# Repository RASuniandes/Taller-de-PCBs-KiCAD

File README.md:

# Taller de PCBs KiCAD — RAS x CERES
**Proyecto de taller (Carrito con ESP32-S3)** · 
23-09-2024: **RAS Day** 🎉

Este repo contiene el material del taller colaborativo **RAS x CERES** de diseño de PCBs en KiCAD:
- Proyecto KiCad listo para abrir (v8+).
- Librerías de símbolos y huellas *incluidas* (rutas relativas).
- Reglas de diseño (DRC) configurables para JLCPCB.
- Gerbers de ejemplo y BOM.

## 🧩 Hardware del proyecto
- **MCU:** ESP32-S3 DevKit C1 (módulo, footprint incluido).
- **IMU:** MPU6050 (módulo).
- **Motores:** Módulo **DRV8833** (Driver de Motores).
- **Expansión I²C:** 3 conectores **JST-XH 4 pines** (VCC, GND, SDA, SCL).
- **Power & Actuadores:**
  - Bornera de tornillo para **batería** (2 + 2 pines).
  - Borneras de tornillo para **motores** (2×2 pines o 2× de 2 pines).

> **Tip de ruta**: el ESP32-S3 DevKit C1 aquí se usa como *módulo* (no el chip suelto), para acelerar footprinting y montaje.

## ⚙️ Requisitos
- **KiCad 8.x** (recomendado).
- Sin dependencias externas: librerías incluidas y referenciadas de forma **relativa**.

## 🚀 Uso rápido
```bash
# 1) Clona
git clone https://github.com/<tu-org-o-user>/Taller-PCBs-KiCAD-RASxCERES.git
cd Taller-PCBs-KiCAD-RASxCERES
```
🧭 Flujo de trabajo en el taller

  1) Esquemático (.kicad_sch):
      Bloques: ESP32S3, DRV8833, I2C_Expanders (3× JST-XH 4p), Power, MPU6050, (opcional) Color.
  
  2) Net labels claras: I2C_SDA, I2C_SCL, M1_A, M1_B, M2_A, M2_B, VBAT, 5V, 3V3, GND.
  3) Asignación de huellas (ya pre-asignadas; revisar conflictos si cambias referencias).
  4) Reglas/DRC: cargar kicad/rules/jlcpcb.kicad_dru.
  5) Ruteo: intenta mantener I²C corto y motores con pistas anchas.
  6) Fabricación: exporta Gerbers a kicad/fabrication/ o usa los de ejemplo

🤝 Créditos

Taller colaborativo [(RAS)](https://www.instagram.com/ras_uniandes/?hl=en) x CERES [(@ceres.robotics)](https://www.instagram.com/ceres.robotics/?hl=en)

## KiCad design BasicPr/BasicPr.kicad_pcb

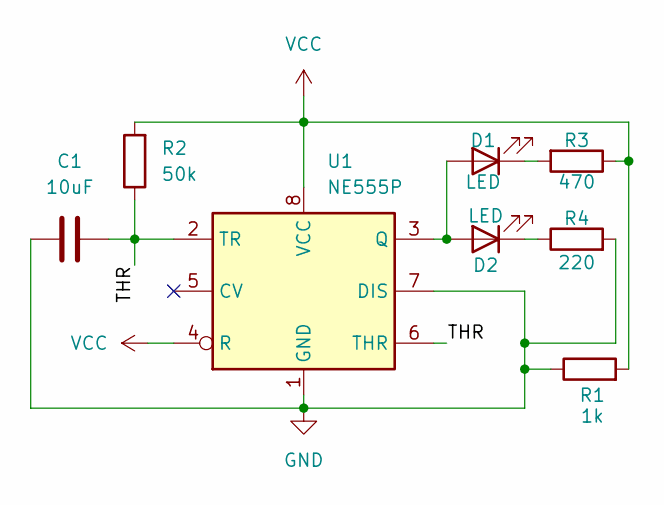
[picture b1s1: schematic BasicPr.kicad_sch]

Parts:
C1: 10uF; CP_Radial_D5.0mm_P2.50mm
D1, D2: LED; LED_D3.0mm_Horizontal_O1.27mm_Z10.0mm
R1: 1k; R_Axial_DIN0204_L3.6mm_D1.6mm_P7.62mm_Horizontal
R2: 50k; R_Axial_DIN0204_L3.6mm_D1.6mm_P7.62mm_Horizontal
R3: 470; R_Axial_DIN0204_L3.6mm_D1.6mm_P7.62mm_Horizontal
R4: 220; R_Axial_DIN0204_L3.6mm_D1.6mm_P7.62mm_Horizontal
U1: NE555P; DIP-8_W7.62mm

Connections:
/THR: C1.1, R2.1, U1.2 (TR), U1.6 (THR)
GND: C1.2, R1.1, R4.2, U1.1 (GND), U1.7 (DIS)
unnamed: D1.2 (A), D2.2 (A), U1.3 (Q)
unnamed: D1.1 (K), R3.2
unnamed: D2.1 (K), R4.1
VCC: R1.2, R2.2, R3.1, U1.4 (R), U1.8 (VCC)

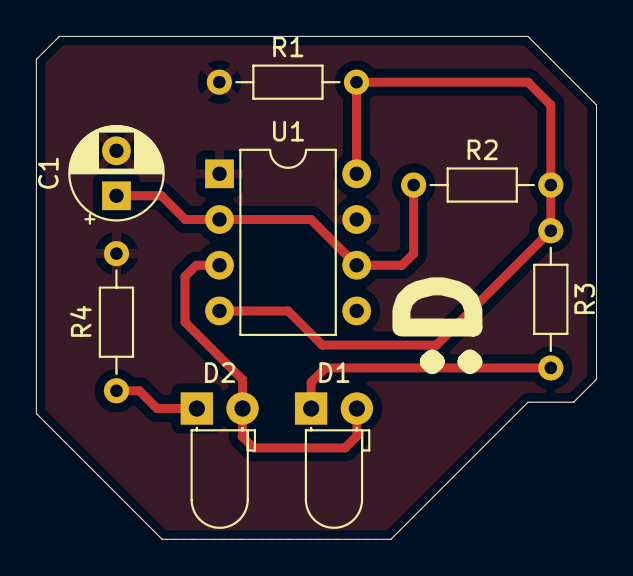
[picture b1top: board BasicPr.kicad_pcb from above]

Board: 2 copper layers, 31.1 x 27.9 mm, 8 parts (0 on the bottom side), 6 nets.

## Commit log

2025-09-01 Footprints & Basic Example
2025-09-02 PCB Básica Final
